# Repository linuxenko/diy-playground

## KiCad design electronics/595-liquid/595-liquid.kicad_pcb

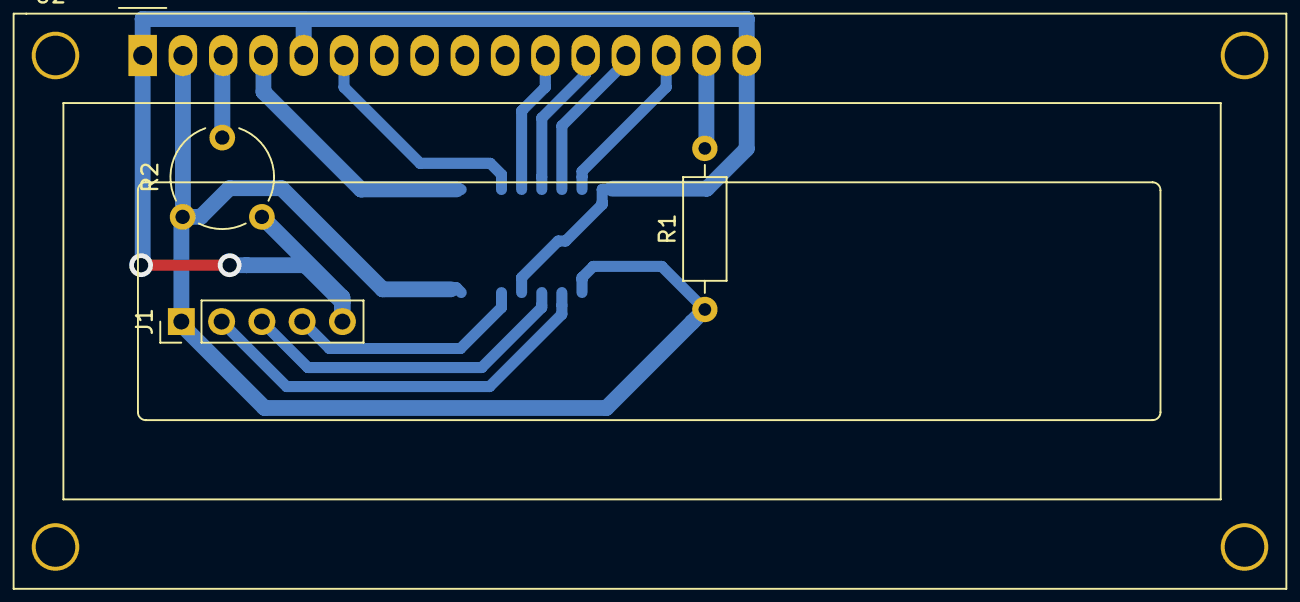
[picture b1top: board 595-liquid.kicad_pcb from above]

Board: 2 copper layers, 5 parts (1 on the bottom side), 13 nets.

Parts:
J1: Conn_01x05_Male; PinHeader_1x05_P2.54mm_Vertical
R1: 220; R_Axial_DIN0207_L6.3mm_D2.5mm_P10.16mm_Horizontal
R2: 5K; Potentiometer_Piher_PT-6-V_Vertical
U1: 74HC595; SOP-16_4.55x10.3mm_P1.27mm
U2: RC1602A; WC1602A

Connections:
+5V: J1.1, R1.1, R2.3, U1.10, U1.16, U2.2
GND: J1.5, R2.1, U1.8, U1.13, U2.1, U2.5, U2.16
unnamed: J1.2, U1.11
unnamed: J1.3, U1.12
unnamed: J1.4, U1.14
unnamed: R1.2, U2.15
unnamed: R2.2, U2.3
unnamed: U1.1, U2.4
unnamed: U1.3, U2.6
unnamed: U1.4, U2.11
unnamed: U1.5, U2.12
unnamed: U1.6, U2.13
unnamed: U1.7, U2.14

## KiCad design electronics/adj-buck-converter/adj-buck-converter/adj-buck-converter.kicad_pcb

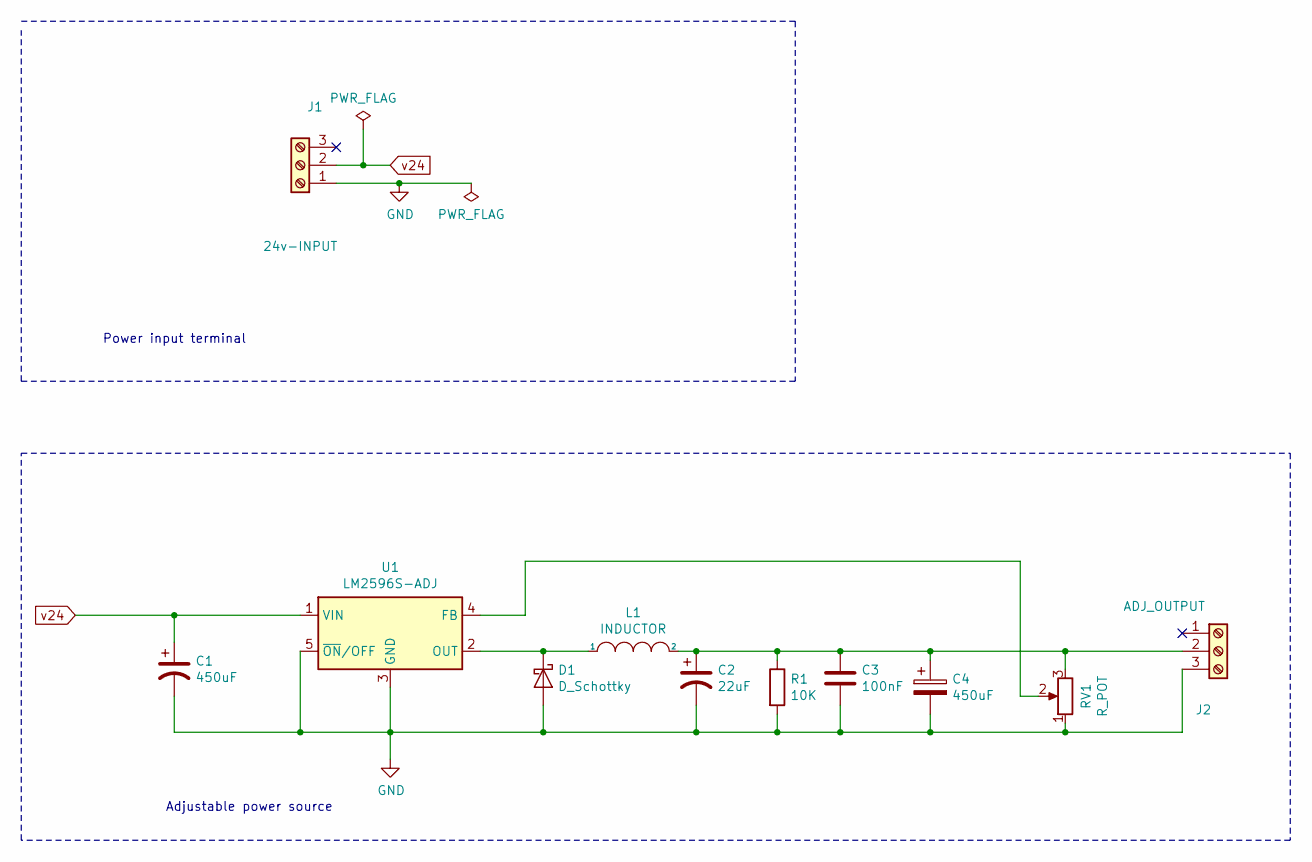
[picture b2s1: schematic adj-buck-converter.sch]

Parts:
C1, C4: 450uF; CP_Radial_D8.0mm_P3.50mm
C2: 22uF; CP_Radial_D8.0mm_P3.50mm
C3: 100nF; C_Disc_D4.3mm_W1.9mm_P5.00mm
D1: D_Schottky; D_A-405_P10.16mm_Horizontal
J1: 24v-INPUT; PhoenixContact_MCV_1,5_3-G-5.08_1x03_P5.08mm_Vertical
J2: ADJ_OUTPUT; PhoenixContact_MCV_1,5_3-G-5.08_1x03_P5.08mm_Vertical
L1: INDUCTOR; L_Toroid_Horizontal_D6.5mm_P10.00mm_Diameter7-5mm_Amidon-T25
R1: 10K; R_Axial_DIN0207_L6.3mm_D2.5mm_P10.16mm_Horizontal
RV1: R_POT; Potentiometer_Piher_PC-16_Single_Horizontal
U1: LM2596S-ADJ; TO-263-5_TabPin3

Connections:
GND: C1.2, C2.2, C3.2, C4.2, D1.2 (A), J1.1, J2.3, R1.2, RV1.1, U1.3 (GND), U1.5 (~ON~/OFF)
unnamed: C2.1, C3.1, C4.1, J2.2, L1.2, R1.1, RV1.3
unnamed: D1.1 (K), L1.1, U1.2 (OUT)
unnamed: RV1.2, U1.4 (FB)
v24: C1.1, J1.2, U1.1 (VIN)

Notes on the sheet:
Adjustable power source
Power input terminal

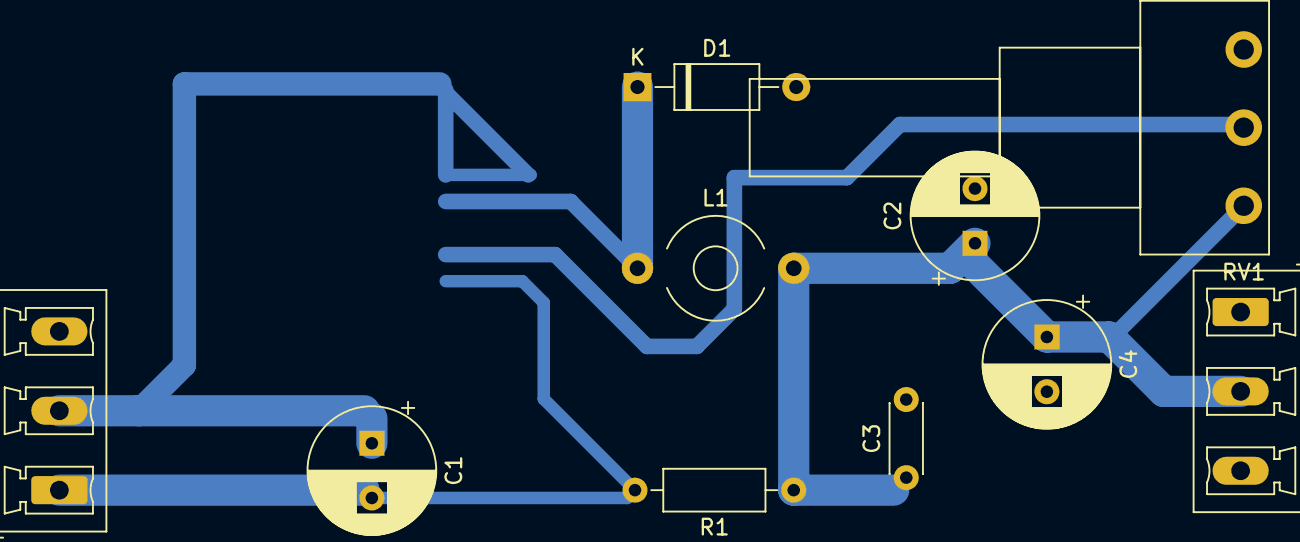
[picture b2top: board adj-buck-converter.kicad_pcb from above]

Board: 2 copper layers, 11 parts (1 on the bottom side), 5 nets.

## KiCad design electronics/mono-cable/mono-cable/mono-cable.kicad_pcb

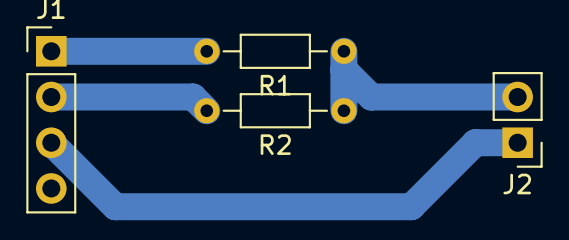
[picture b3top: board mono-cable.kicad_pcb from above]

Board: 2 copper layers, 4 parts (0 on the bottom side), 4 nets.

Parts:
J1: Conn_01x04_Male; PinHeader_1x04_P2.54mm_Vertical
J2: Conn_01x02_Male; PinHeader_1x02_P2.54mm_Vertical
R1, R2: 220; R_Axial_DIN0204_L3.6mm_D1.6mm_P7.62mm_Horizontal

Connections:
GND: J1.3, J1.4, J2.1
unnamed: J1.1, R1.2
unnamed: J1.2, R2.2
unnamed: J2.2, R1.1, R2.1

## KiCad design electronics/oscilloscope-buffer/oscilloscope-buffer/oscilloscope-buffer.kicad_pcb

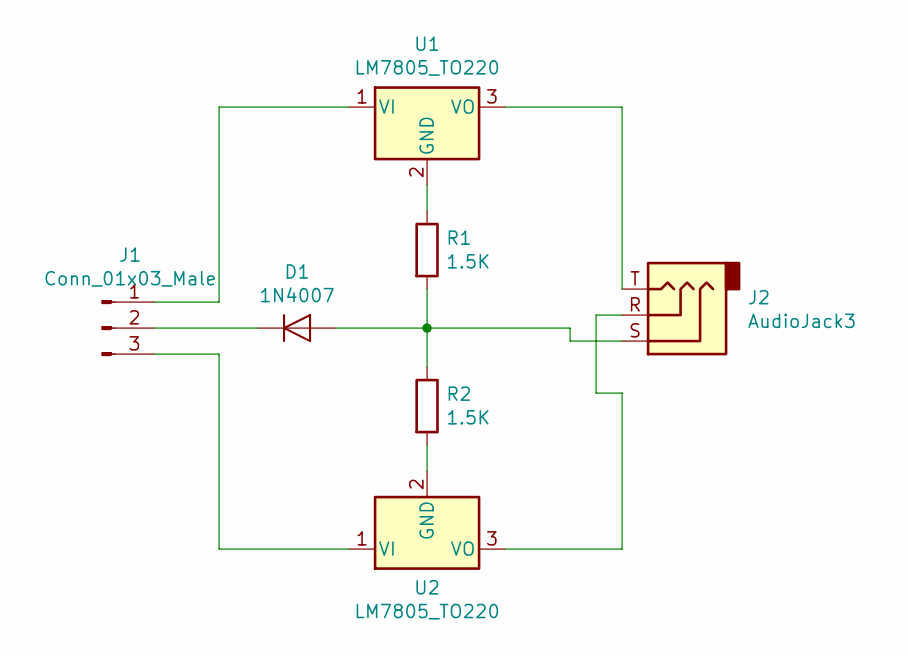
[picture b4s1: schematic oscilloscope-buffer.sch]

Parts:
D1: 1N4007; D_DO-41_SOD81_P10.16mm_Horizontal
J1: Conn_01x03_Male; PinHeader_1x03_P2.54mm_Vertical
J2: AudioJack3; Jack_3.5mm_Ledino_KB3SPRS_Horizontal
R1, R2: 1.5K; R_Axial_DIN0204_L3.6mm_D1.6mm_P7.62mm_Horizontal
U1, U2: LM7805_TO220; TO-220-3_Vertical

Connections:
unnamed: D1.1 (K), J1.2
unnamed: D1.2 (A), J2.S, R1.2, R2.1
unnamed: J1.1, U1.1 (VI)
unnamed: J1.3, U2.1 (VI)
unnamed: J2.R, U2.3 (VO)
unnamed: J2.T, U1.3 (VO)
unnamed: R1.1, U1.2 (GND)
unnamed: R2.2, U2.2 (GND)

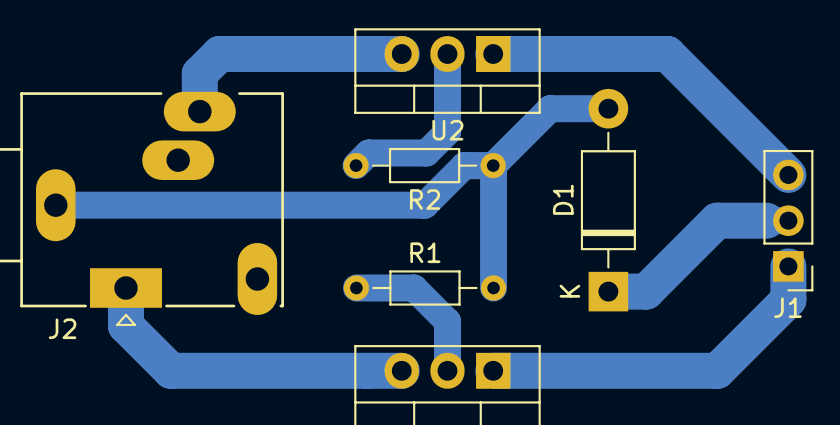
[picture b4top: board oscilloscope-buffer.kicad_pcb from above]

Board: 2 copper layers, 7 parts (0 on the bottom side), 8 nets.

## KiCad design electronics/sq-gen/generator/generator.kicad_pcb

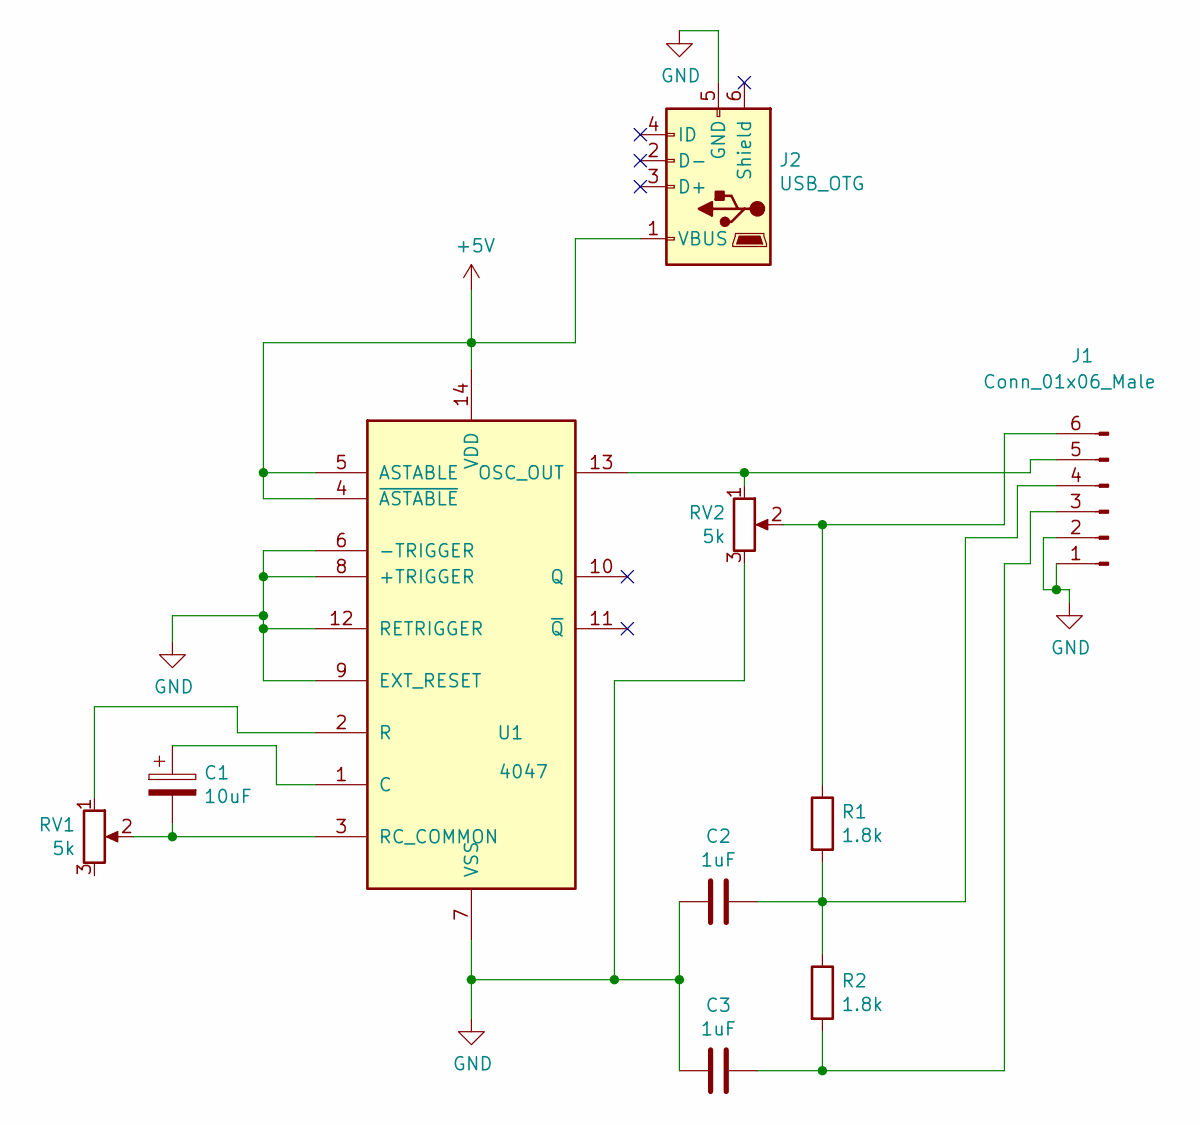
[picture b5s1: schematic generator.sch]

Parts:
C1: 10uF; CP_Radial_D5.0mm_P2.50mm
C2, C3: 1uF; C_Axial_L12.0mm_D6.5mm_P15.00mm_Horizontal
J1: Conn_01x06_Male; PinHeader_1x06_P2.54mm_Vertical
J2: USB_OTG; USB_Micro_1_27x5
R1, R2: 1.8k; R_Axial_DIN0204_L3.6mm_D1.6mm_P7.62mm_Horizontal
RV1, RV2: 5k; Potentiometer_Piher_T-16H_Single_Horizontal
U1: 4047; DIP-14_W7.62mm

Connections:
+5V: J2.1 (VBUS), U1.4 (~ASTABLE), U1.5 (ASTABLE), U1.14 (VDD)
GND: C2.2, C3.2, J1.1, J1.2, J2.5 (GND), RV2.3, U1.6 (-TRIGGER), U1.7 (VSS), U1.8 (+TRIGGER), U1.9 (EXT_RESET), U1.12 (RETRIGGER)
unnamed: C1.1, U1.1 (C)
unnamed: C1.2, RV1.2, U1.3 (RC_COMMON)
unnamed: C2.1, J1.4, R1.2, R2.1
unnamed: C3.1, J1.3, R2.2
unnamed: J1.5, RV2.1, U1.13 (OSC_OUT)
unnamed: J1.6, R1.1, RV2.2
unnamed: RV1.1, U1.2 (R)

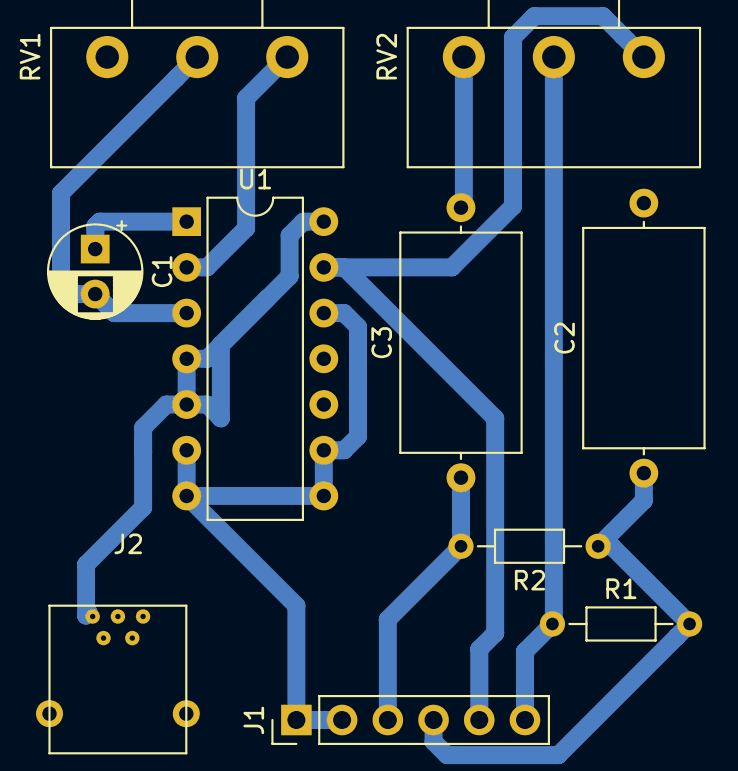
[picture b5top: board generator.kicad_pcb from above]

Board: 2 copper layers, 10 parts (0 on the bottom side), 9 nets.

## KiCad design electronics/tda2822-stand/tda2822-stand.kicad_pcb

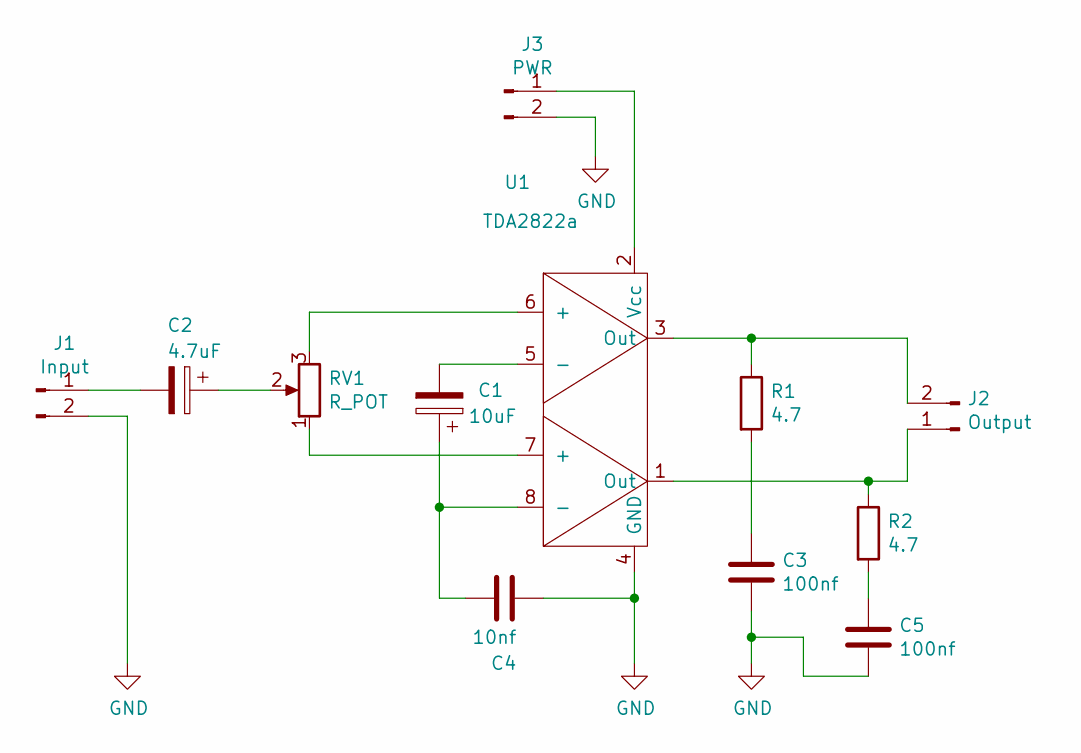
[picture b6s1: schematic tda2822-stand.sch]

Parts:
C1: 10uF; CP_Radial_D8.0mm_P3.50mm
C2: 4.7uF; CP_Radial_D8.0mm_P3.50mm
C3, C5: 100nf; C_Disc_D4.3mm_W1.9mm_P5.00mm
C4: 10nf; C_Disc_D4.3mm_W1.9mm_P5.00mm
J1: Input; PinHeader_1x02_P2.54mm_Vertical
J2: Output; PinHeader_1x02_P2.54mm_Vertical
J3: PWR; PinHeader_1x02_P2.54mm_Vertical
R1, R2: 4.7; R_Axial_DIN0207_L6.3mm_D2.5mm_P15.24mm_Horizontal
RV1: R_POT; Potentiometer_Piher_T-16H_Single_Horizontal
U1: TDA2822a; SO-8_3.9x4.9mm_P1.27mm

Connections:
GND: C3.2, C4.2, C5.2, J1.2, J3.2, U1.4 (GND)
unnamed: C1.1, C4.1, U1.8 (-)
unnamed: C1.2, U1.5 (-)
unnamed: C2.1, RV1.2
unnamed: C2.2, J1.1
unnamed: C3.1, R1.2
unnamed: C5.1, R2.2
unnamed: J2.1, R2.1, U1.1 (Out)
unnamed: J2.2, R1.1, U1.3 (Out)
unnamed: J3.1, U1.2 (Vcc)
unnamed: RV1.1, U1.7 (+)
unnamed: RV1.3, U1.6 (+)

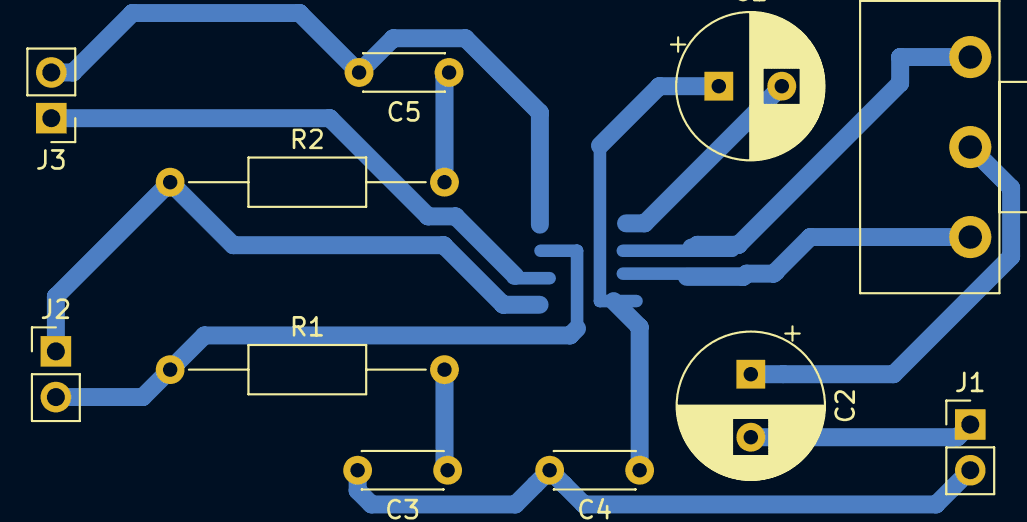
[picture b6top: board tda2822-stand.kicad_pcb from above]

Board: 2 copper layers, 12 parts (1 on the bottom side), 12 nets.

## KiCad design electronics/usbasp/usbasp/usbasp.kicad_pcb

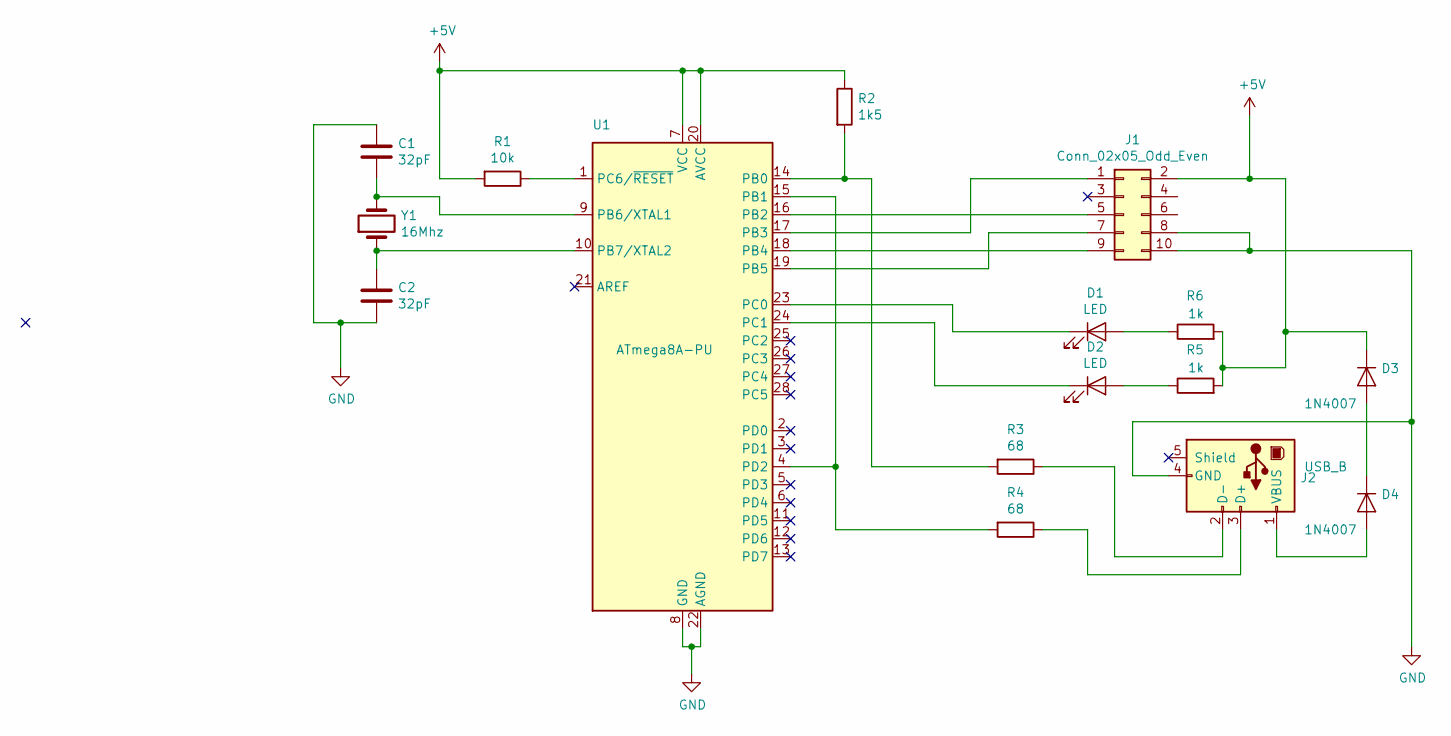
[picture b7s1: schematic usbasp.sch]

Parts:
C1, C2: 32pF; C_Disc_D3.0mm_W1.6mm_P2.50mm
D1, D2: LED; LED_D3.0mm_FlatTop
D3, D4: 1N4007; D_DO-35_SOD27_P7.62mm_Horizontal
J1: Conn_02x05_Odd_Even; PinHeader_2x05_P2.54mm_Vertical
J2: USB_B; USB_B_OST_USB-B1HSxx_Horizontal
R1: 10k; R_Axial_DIN0204_L3.6mm_D1.6mm_P7.62mm_Horizontal
R2: 1k5; R_Axial_DIN0204_L3.6mm_D1.6mm_P7.62mm_Horizontal
R3, R4: 68; R_Axial_DIN0204_L3.6mm_D1.6mm_P7.62mm_Horizontal
R5, R6: 1k; R_Axial_DIN0204_L3.6mm_D1.6mm_P7.62mm_Horizontal
U1: ATmega8A-PU; DIP-28_W7.62mm
Y1: 16Mhz; Crystal_HC49-4H_Vertical

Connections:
+5V: D3.1 (K), J1.2, R1.2, R2.1, R5.2, R6.2, U1.7 (VCC), U1.20 (AVCC)
GND: C1.1, C2.2, J1.8, J1.10, J2.4 (GND), U1.8 (GND), U1.22 (AGND)
unnamed: C1.2, U1.9 (PB6/XTAL1), Y1.2
unnamed: C2.1, U1.10 (PB7/XTAL2), Y1.1
unnamed: D1.1 (K), U1.23 (PC0)
unnamed: D1.2 (A), R6.1
unnamed: D2.1 (K), U1.24 (PC1)
unnamed: D2.2 (A), R5.1
unnamed: D3.2 (A), D4.1 (K)
unnamed: D4.2 (A), J2.1 (VBUS)
unnamed: J1.1, U1.17 (PB3)
unnamed: J1.5, U1.16 (PB2)
unnamed: J1.7, U1.19 (PB5)
unnamed: J1.9, U1.18 (PB4)
unnamed: J2.2 (D-), R3.1
unnamed: J2.3 (D+), R4.1
unnamed: R1.1, U1.1 (PC6/~RESET)
unnamed: R2.2, R3.2, U1.14 (PB0)
unnamed: R4.2, U1.4 (PD2), U1.15 (PB1)

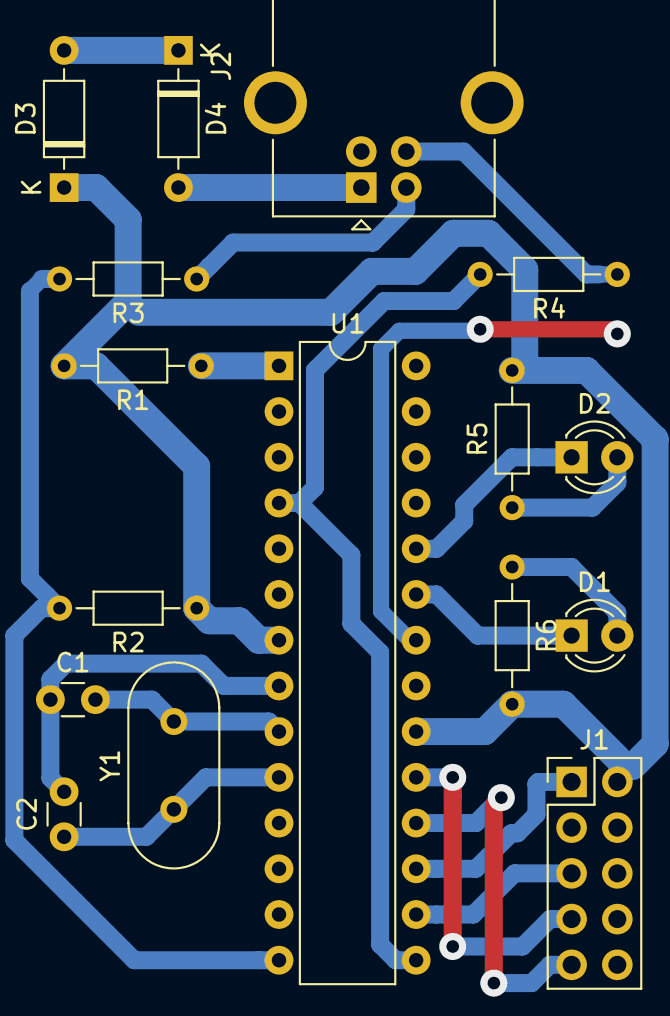
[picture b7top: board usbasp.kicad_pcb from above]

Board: 2 copper layers, 16 parts (0 on the bottom side), 19 nets.
